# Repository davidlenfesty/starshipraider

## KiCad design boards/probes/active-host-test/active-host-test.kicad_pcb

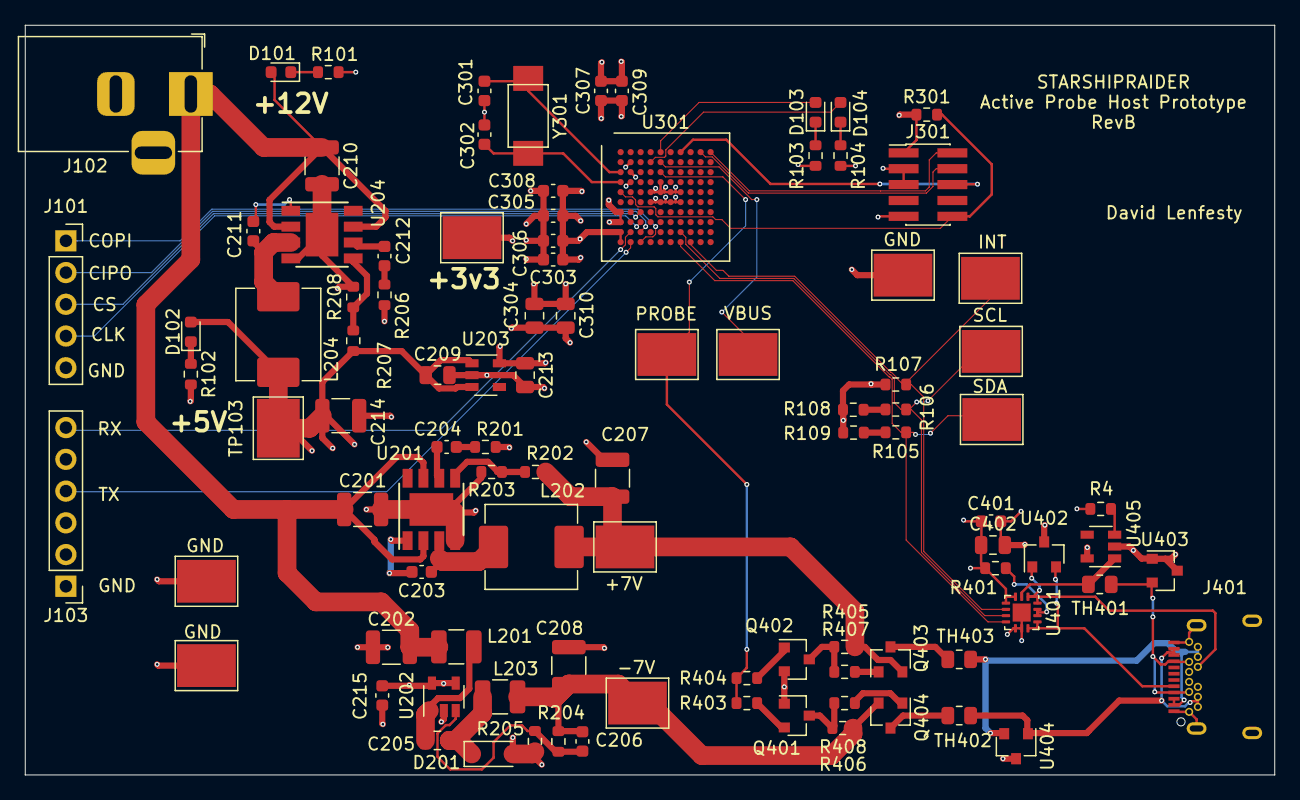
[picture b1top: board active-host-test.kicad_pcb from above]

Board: 4 copper layers, 100.0 x 60.0 mm, 97 parts (0 on the bottom side), 60 nets.

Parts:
C201, C202, C208, C210: 22u; C_1210_3225Metric
C203, C211, C306: 10n; C_0603_1608Metric
C204, C212: 6n8; C_0603_1608Metric
C205, C209, C213, C304, C310, C402: 1u; C_0805_2012Metric
C206: 330p; C_0603_1608Metric
C207, C214: 47u; C_1210_3225Metric
C215, C303, C305, C307, C308, C309, C401: 0u1; C_0603_1608Metric
C301, C302: 10p; C_0603_1608Metric
D101, D102, D103, D104: LED; LED_0603_1608Metric
D201: MBR0520; D_SOD-123
J101: Conn_01x05_Male; PinSocket_1x05_P2.54mm_Vertical
J102: Barrel_Jack; BarrelJack_Horizontal
J103: Conn_01x06_Male; PinHeader_1x06_P2.54mm_Vertical
J301: Conn_ARM_JTAG_SWD_10; PinHeader_2x05_P1.27mm_Vertical_SMD
J401: USB_C_Receptacle; 10137062
L201, L203: 22u; L_1210_3225Metric
L202, L204: 12u; L_Abracon_ASPI-0630LR
Q401: Q_PNP_BEC; SOT-23
Q402: Q_NPN_BEC; SOT-23
Q403: Q_PMOS_GSD; SOT-23
Q404: Q_NMOS_GSD; SOT-23
R4, R101, R102, R107, R203, R205, R208, R301, R403, R404, R405, R406: 10k; R_0603_1608Metric
R103, R104, R105, R106, R108, R109: 1k; R_0603_1608Metric
R201, R206: 6k8; R_0603_1608Metric
R202: 66k; R_0603_1608Metric
R204: 47k; R_0603_1608Metric
R207: 44k; R_0603_1608Metric
R401: 0R; R_0603_1608Metric
R407, R408: 100R; R_0603_1608Metric
TH401, TH402, TH403: Thermistor_PTC; R_0805_2012Metric
TP101, TP102, TP103, TP104, TP105, TP106, TP107, TP108, TP109, TP110, TP111, TP112: TestPoint; Keystone_5016
U201, U204: AP6502; Diodes_SO-8EP
U202: LM2611xMF; SOT-23-5
U203: AP2112K-3.3; SOT-23-5
U301: STM32F103V8Hx; LFBGA-100_10x10mm_Layout10x10_P0.8mm
U401: FUSB302BMPX; WQFN-14-1EP_2.5x2.5mm_P0.5mm_EP1.45x1.45mm
U402: STS232033B102; SOT-23
U403: STS232050B751; SOT-23
U404: STS232120B301; SOT-23
U405: TPS2051C; SOT-23-5
Y301: 8MHz; Crystal_NX5032

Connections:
+3V3: C213.1, C303.1, C304.1, C305.1, C306.1, C307.1, C308.1, C309.1, C310.1, J301.1, R107.2, R108.2, R109.2, R301.1, TP104.1, U203.5, U301.B2, U301.D2, U301.F4, U301.F5, U301.F6, U301.F7, U301.J1, U301.K1
+5V: C209.1, C214.1, C215.1, C401.1, C402.1, D102.2, L204.2, R4.2, R207.1, R401.1, TP103.1, U202.4, U202.5, U203.1, U203.3, U401.3, U401.4, U405.5
/+7V: C207.1, L202.2, Q403.2, R202.1, R405.1, TP101.1
/+12V: C201.1, C202.1, C210.1, D101.2, J102.1, L201.1, U201.2, U201.7, U204.2, U204.7
/-7V: C206.1, C208.1, L203.2, Q404.2, R204.1, R406.2, TP102.1
/I2C_SCL: R106.1, TP108.1, U301.J7, U401.6
/I2C_SDA: R105.1, TP107.1, U301.K7, U401.7
/I2C_~INT: R107.1, TP109.1, U301.K8, U401.5
/MCU/NRST: J301.10, R301.2, U301.E1
/MCU/SWCLK: J301.4, U301.A9
/MCU/SWDIO: J301.2, U301.A10
/MCU/SWO: J301.6, U301.A7
/MCU/UART_RX: J103.4, U301.K2
/MCU/UART_TX: J103.6, U301.J2
/PROBE_PWR_EN: R403.2, R404.2, TP105.1, U301.C5
/PROBE_VBUS_~EN: TP106.1, U301.B5
/SPI_CIPO: J101.2, U301.J3
/SPI_CLK: J101.4, U301.H3
/SPI_COPI: J101.1, U301.K3
/SPI_~CS: J101.3, U301.G3
/USB C/+7V_FUSED: J401.A2, J401.A3, J401.B2, J401.B3, TH403.1, U404.2
/USB C/+7V_GATED: Q403.3, TH403.2
/USB C/-7V_FUSED: J401.A10, J401.A11, J401.B10, J401.B11, TH402.2, U404.1
/USB C/-7V_GATED: Q404.3, TH402.1
/USB C/CC1: J401.A5, U401.10, U401.11, U402.2
/USB C/CC2: J401.B5, U401.1, U401.14, U402.1
/USB C/VBUS: TH401.1, U401.2, U405.1
/USB C/VBUS_FUSED: J401.A4, J401.A9, J401.B4, J401.B9, TH401.2, U403.2
/USRLED1: D103.2, U301.A5
/USRLED2: D104.2, U301.B4
GND: C201.2, C202.2, C207.2, C208.2, C209.2, C210.2, C213.2, C214.2, C215.2, C301.2, C302.2, C303.2, C304.2, C305.2, C306.2, C307.2, C308.2, C309.2, C310.2, C401.2, C402.2, D201.2, J101.5, J102.2, J103.1, J301.3, J301.5, J301.9, J401.A1, J401.A12, J401.B1, J401.B12, J401.S1, Q401.1, Q402.2, R101.2, R102.2, R103.2, R104.2, R201.2, R203.2, R205.2, R206.2, R208.2, TP110.1, TP111.1, TP112.1, U201.4, U201.9, U202.2, U203.2, U204.4, U204.9, U301.C2, U301.D5, U301.E4, U301.E5, U301.E6, U301.E7, U301.G1, U301.H1, U401.8, U401.9, U401.15, U402.3, U403.1, U403.3, U404.3, U405.2
unnamed: C203.1, U201.1
unnamed: C203.2, L202.1, U201.3
unnamed: C204.1, U201.6
unnamed: C204.2, R201.1
unnamed: C205.1, D201.1, L203.1
unnamed: C205.2, L201.2, U202.1
unnamed: C206.2, R204.2, R205.1, U202.3
unnamed: C211.1, U204.1
unnamed: C211.2, L204.1, U204.3
unnamed: C212.1, U204.6
unnamed: C212.2, R206.1
unnamed: C301.1, U301.C1, Y301.1
unnamed: C302.1, U301.D1, Y301.2
unnamed: D101.1, R101.1
unnamed: D102.1, R102.1
unnamed: D103.1, R103.1
unnamed: D104.1, R104.1
unnamed: Q401.2, R403.1
unnamed: Q401.3, R406.1, R408.2
unnamed: Q402.1, R404.1
unnamed: Q402.3, R405.2, R407.2
unnamed: Q403.1, R407.1
unnamed: Q404.1, R408.1
unnamed: R4.1, U405.3
unnamed: R105.2, R109.1
unnamed: R106.2, R108.1
unnamed: R202.2, R203.1, U201.5
unnamed: R207.2, R208.1, U204.5
unnamed: R401.2, U401.12, U401.13

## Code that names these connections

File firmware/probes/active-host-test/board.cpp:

#include "board.h"
#include "pin.h"

#include <stm32f1xx.h>
#include <stm32f1xx_hal.h>
#include <string.h>

I2C_HandleTypeDef i2c_fusb;

namespace Board {

/// Set up clocks for HSE, providing 72MHz sys clock
void clock_init() {
    //RCC_PLLInitTypeDef pll_cfg;
    //pll_cfg.PLLMUL = RCC_PLL_MUL9;
    //pll_cfg.PLLSource = RCC_PLLSOURCE_HSE;
    //pll_cfg.PLLState = RCC_PLL_ON;

    //RCC_OscInitTypeDef osc_cfg;
    //osc_cfg.HSEState = RCC_HSE_ON;
    //osc_cfg.HSEPredivValue = RCC_HSE_PREDIV_DIV1;
    //osc_cfg.PLL = pll_cfg;

    //// Turn HSE on along with PLL
    //osc_cfg.OscillatorType = RCC_OSCILLATORTYPE_HSE;
    //HAL_RCC_OscConfig(&osc_cfg);

    //// Select PLL as clock source for the system clock
    //RCC_ClkInitTypeDef clk_cfg;
    //clk_cfg.ClockType = RCC_CLOCKTYPE_SYSCLK | RCC_CLOCKTYPE_HCLK | RCC_CLOCKTYPE_PCLK1 | RCC_CLOCKTYPE_PCLK2;
    //clk_cfg.SYSCLKSource = RCC_SYSCLKSOURCE_PLLCLK; // Get SYSCLK from 72MHz PLL
    //clk_cfg.AHBCLKDivider = RCC_SYSCLK_DIV1;        // 72MHz HCLK
    //clk_cfg.APB1CLKDivider = RCC_HCLK_DIV2;         // 36MHz PCLK1
    //clk_cfg.APB2CLKDivider = RCC_HCLK_DIV2;         // 36MHz PCLK2
    //HAL_RCC_ClockConfig(&clk_cfg, 2); // Unsure about flash latency

    // Enable peripheral clocks
    __HAL_RCC_USART1_CLK_ENABLE();
    __HAL_RCC_I2C1_CLK_ENABLE();
    __HAL_RCC_I2C2_CLK_ENABLE();
    __HAL_RCC_SPI1_CLK_ENABLE();
    __HAL_RCC_SPI2_CLK_ENABLE();
    __HAL_RCC_GPIOA_CLK_ENABLE();
    __HAL_RCC_GPIOB_CLK_ENABLE();
    __HAL_RCC_AFIO_CLK_ENABLE();
}

void i2c_init() {
    i2c_fusb.Instance               = I2C2;

    i2c_fusb.Init.ClockSpeed        = 400000; // FUSB302 must be run at a minimum of 400kHz
    i2c_fusb.Init.DutyCycle         = I2C_DUTYCYCLE_2; // TODO do I care about this?
    i2c_fusb.Init.OwnAddress1       = 0;
    i2c_fusb.Init.AddressingMode    = I2C_ADDRESSINGMODE_7BIT;
    i2c_fusb.Init.DualAddressMode   = I2C_DUALADDRESS_DISABLED;
    i2c_fusb.Init.OwnAddress2       = 0;
    i2c_fusb.Init.GeneralCallMode   = I2C_GENERALCALL_DISABLED;
    i2c_fusb.Init.NoStretchMode     = I2C_NOSTRETCH_DISABLED;

    HAL_I2C_Init(&i2c_fusb);
}

void spi_init() {
    __HAL_RCC_SPI1_CLK_ENABLE();
    __HAL_RCC_SPI1_FORCE_RESET();
    __HAL_RCC_SPI1_RELEASE_RESET();

    // Initialize pins. These objects get destroyed but I don't care.
    Drivers::Pin spi_nss(GPIOA, GPIO_PIN_4, GPIO_MODE_AF_INPUT, GPIO_PULLUP);
    Drivers::Pin spi_clk(GPIOA, GPIO_PIN_5, GPIO_MODE_AF_INPUT, GPIO_NOPULL);
    Drivers::Pin spi_cipo(GPIOA, GPIO_PIN_6, GPIO_MODE_AF_PP, GPIO_NOPULL);
    Drivers::Pin spi_copi(GPIOA, GPIO_PIN_7, GPIO_MODE_AF_INPUT, GPIO_NOPULL);

    // Configure EXTI to detect CS flips on GPIOA4
    EXTI->IMR = EXTI_IMR_IM4;       // Enable interrupts
    EXTI->FTSR = EXTI_FTSR_FT4;     // Set falling trigger

    // 8-bit mode, 0 polarity/0 phase, slave, no CRC and disabled.
    SPI1->CR1 = 0;
    // Only enable RX interrupt
    SPI1->CR2 = SPI_CR2_RXNEIE;
    // Start SPI
    SPI1->CR1 |= SPI_CR1_SPE;

    // Preload data registers with 0's.
    // Must be set before receiving.
    SPI1->DR = 0x00;

    // Enable interrupts
    NVIC_SetPriority(SPI1_IRQn, 0);
    NVIC_SetPriority(EXTI4_IRQn, 0);
    NVIC_EnableIRQ(SPI1_IRQn);
    NVIC_EnableIRQ(EXTI4_IRQn);
}

constexpr uint8_t fusb_addr = 0x44;

// TODO I don't think this works...
// Need to do repeated START, etc
uint8_t i2c_read_register(uint8_t reg, uint8_t len, uint8_t* const data) {
    HAL_I2C_Mem_Read(&i2c_fusb, fusb_addr, reg, I2C_MEMADD_SIZE_8BIT, data, len, 1000);
    return len;
}

uint8_t i2c_write_register(uint8_t reg, uint8_t len, uint8_t* const data) {
    HAL_I2C_Mem_Write(&i2c_fusb, fusb_addr, reg, I2C_MEMADD_SIZE_8BIT, data, len, 1000);
    return len;
}

Drivers::Pin probe_pwr_en;
Drivers::Pin probe_vbus_nen;

void pwr_init() {
    // TODO is this doing what I want? I.e. leaving uninitialized until pwr_init is called
    probe_pwr_en = Drivers::Pin(GPIOB, GPIO_PIN_5, GPIO_MODE_OUTPUT_PP, GPIO_NOPULL, GPIO_PIN_RESET);
    //probe_vbus_nen = Drivers::Pin(GPIOB, GPIO_PIN_6, GPIO_MODE_OUTPUT_PP, GPIO_NOPULL, GPIO_PIN_SET);
    probe_vbus_nen = Drivers::Pin(GPIOB, GPIO_PIN_6, GPIO_MODE_OUTPUT_PP, GPIO_NOPULL, GPIO_PIN_RESET);
}

void pwr_write_cb(uint8_t channel, uint8_t* data) {
    probe_pwr_en.write((bool)*data & 0x01);
    probe_vbus_nen.write(!((bool)*data & 0x02));
}

void pwr_enable(bool en) {
    probe_pwr_en.write(en);
    probe_vbus_nen.write(en);
}

} // namespace Board

// ---- Pin Initialization MSP functions ---- //
// Required by ST HAL
extern "C" {

void HAL_I2C_MspInit(I2C_HandleTypeDef *hi2c) {
    // This will be filled in with all channels info once we write final fw.
    // Or not, and the stm32-cpp port will be written first.
    if (hi2c == &i2c_fusb) {
        GPIO_InitTypeDef gpio;
        gpio.Mode = GPIO_MODE_AF_OD;
        gpio.Pull = GPIO_NOPULL;
        gpio.Speed = GPIO_SPEED_FREQ_LOW;
        gpio.Pin = GPIO_PIN_10 | GPIO_PIN_11;
        HAL_GPIO_Init(GPIOB, &gpio);
    } else {
        // TODO assert
    }
}

}

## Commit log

2021-01-11 saving state
2021-01-12 active-host-fw: moved to ST HAL and made some progress
2021-01-13 active-host-fw: friendship ended with Make, now cmake is my best friend
2021-01-13 active-host-fw: more progress on USB C side of FUSB302 lib
2021-01-13 active-host-fw: done all the USB-C stuff I think I need for the test
    Lots of PD settings to expose but I think I can use mostly the defaults
    there as well. Most of the effort will be wrangling the protocol and
    in-line commands that the FUSB302 expects
2021-01-13 active-host-fw: USB PD mostly done
    (at least for the stuff I care about in the prototype)
2021-01-13 active-host-fw: fix I2C read/write functions
2021-01-14 active-host-fw: finish all the FUSB stuff I think I need
2021-01-14 active-host-fw: started work on PD-level stuff
2021-01-21 active probes tests: exact boards being sent to fab
2021-01-30 active-host-fw: lots of progress towards SPI register interface
    A bit more work on types and then I can start hooking it into the proper
    application code, and at that point I'm writing the actual business
    logic, which *shouldn't* take too long. Probably will because that
    includes dealing with USB PD.
2021-02-07 active-host-fw: just need to finish registers and VDM interface
2021-02-08 First pass at defining active probe USB C interface.
2021-02-14 active-host-test: Fix issues with -7V supply
    - Missing diode for Cuk converter
    - Core needs to operate on 5V, not 12V
2021-02-14 active-host-test: basic bring up (w/o 8MHz crystal)
    List of changes that were essential:
    - linker script was wrong, using one included in HAL temporarily
    - wasn't actually linking against the script
    - need a delay before I2C init for some reason
    - needed to define SysTick_Handler
2021-02-16 active-host-fw: theoretically ready for test
2021-03-15 [TESTING] *so* close to working, just pushing in case anyone can see what I'm doing wrong
2021-03-15 minor FUSB302 driver tweaks
2021-03-23 probes/active-host-test: added errata and fixed some revA bugs
    - replaced lm66100 w/ proper VBUS switch
    - increased I2C pullup strength
2021-03-23 Imported USB PD library (originally from Chromium EC project)
    I just got it to work and transmit PD. Lots of cleanup to do of the
    library and the support files, as well as licensing.
    A bit of work too to either finish the tcpm_driver or modify the library
    to not use tcpc_xfer.
